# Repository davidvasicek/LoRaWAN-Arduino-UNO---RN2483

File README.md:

# LoRaWAN-Arduino-UNO---RN2483

### Cíl projektu

Tento projekt byl vytvořen za účelem testování LoRaWAN sítě v oblasti Ostravy, kterou v rámci svých cvičení realizují studenti předmětu Radiokomunikační technika/Rádiové sítě vyučovaného na Katedře telekomunikační techniky, VŠB-TU Ostrava.

V rámci tohoto projektu bylo vytvořeno 8 čidel založených na deskách LoRaWAN Arduino UNO s čipem RN2483 napájených stabilizovaným 3V3 napětím devíti voltové externí baterie a integrovaným MicroUSB konektorem. Každý takovýto modul vysílá prostřednictvím LoRaWAN sítě o frekvenci 868 MHz krátký textový řetězec obsahující svou identifikaci, která je směrována na LoRa Gateway (TTN-GW-VSB) a vizualizována v prostředí The Things Network (TTN). Na základě této komunikace je následně možné určit vysílající výkonovou úrověň daných senzorů a tím vytvořit reálnou mapu pokrytí LoRaWAN sítě dané oblasti.

Pro účely testování bylo zapotřebí obejít Duty Cycle modulu RN2483, který nám omezoval zasílání zpráv v kratších intervalech. Každý takovýto modul RN2483 obsahuje vnitřní čítač zabraňující porušení vysílajících oprávnění přesahující 1% vysílající hodiny. Proto byl modul opakovaně resetován, čímž byl vymazán i jeho vnitřní čítač a tím jsme umožnili testování v kratších časových intervalech.

### Specifikace

LoRaWAN Arduino UNO je malý modulek, na jehož horní straně je transceiver RN2483 firmy Microchip, který je zkomunikovaný s procesorem ATmega328p ležícím na spodní straně desky. V procesoru je bootloader Arduino UNO (možno adaptovat na NANO). Modul je přímo přizpůsoben pro komunikaci v sítích LoRaWAN (více info na things.cz nebo na stránkách Českých Radiokomunikací a.s.). K dispozici jsou tato rozhraní: [1]
-	6 digitálních vstupů/výstupů
-	1 digitální vstup s přerušením pro low power režim
-	1 analogový vstup/výstup
-	vstup pro UART/USB převodník
-	anténní konektor SMA samice (na přání možno osadit U.FL IPX konektorem pro vyvedení antény pigtailem)

**Napájení:**
-	flash mód 5V
-	provozní mód 3,3V (bateriové napájení v rozmezí 2,4V až 4,1V)

**Naměřená spotřeba:**
-	power down mód cca 20uA
-	normální režim cca 25mA
-	vysílací špička cca 120mA

### Tutoriál

Výsledkem tohoto tutoriálu je čidlo založené na desce LoRaWAN Arduino UNO s vysílacím modulem RN2483 umožňující zasílaní krátkých zpráv prostřednictvím bezdrátové technologie LoRa. Tyto zprávy mohou obsahovat například informace o okolních teplotách získávány z externího teplotního senzoru, které je možné k desce LoRaWAN Arduino UNO připojit, nebo informace z mnoha jiných senzorů kompatibilních s touto deskou.

Kompletní tutoriál naleznete ve formátu .pdf [zde](https://github.com/davidvasicek/LoRaWAN-Arduino-UNO---RN2483/blob/master/LoRaWAN-Arduino-UNO---RN2483_tutorial.pdf)
                                                                                        
### Obsah adresáře

- **LoRa_RN5.brd** - DPS LoRaWAN Arduino UNO (Eagle)
- **LoRa_RN5.sch** - schéma LoRaWAN Arduino UNO (Eagle)
- **RN2483-Arduino-Library-master.zip** - knihovna pro RN2483 dostupná [zde](https://github.com/jpmeijers/RN2483-Arduino-Library)
- **LoRaWAN-Arduino-UNO---RN2483_code.ino** - kód pro Arduino IDE
- **LoRaWAN-Arduino-UNO---RN2483_tutorial.pdf** - tutoriál
- **LoRaDHT22** - ukázkový kód pro připojení teplotního čidla DHT22 k LoRaWAN Arduino UNO
- **IMG_LoRaWAN-Arduino-UNO.jpg** - foto vytvořených čidel
- **IMG_LoRaWAN-Arduino-UNO_1.jpg** - foto vytvořených čidel

### Užitečné odkazy

- Specifikace LoRaWAN Arduino UNO - RN2483 - e-shop [zde](https://www.arduinotech.cz/produkt/lorawan-arduino-uno/)
- Specifikace RN2483 [zde](http://ww1.microchip.com/downloads/en/DeviceDoc/50002346C.pdf)
- Popis technologie LoRa [zde](http://www.raycom.cz/data/article/filemanager/LoRa.pdf)
- Článek LPWAN - LoRaWAN, Sigfox - vítejte v IoT! [zde](https://www.arduinotech.cz/inpage/lpwan-lorawan-sigfox-vitejte-v-iot/)
- Článek LoRaWAN Arduino UNO s transceiverem RHF76 [zde](https://www.arduinotech.cz/inpage/lorawan-arduino-uno-s-transceiverem-rhf76/)

### Zdroje

- [1] [https://www.arduinotech.cz/produkt/lorawan-arduino-uno/](https://www.arduinotech.cz/produkt/lorawan-arduino-uno/)

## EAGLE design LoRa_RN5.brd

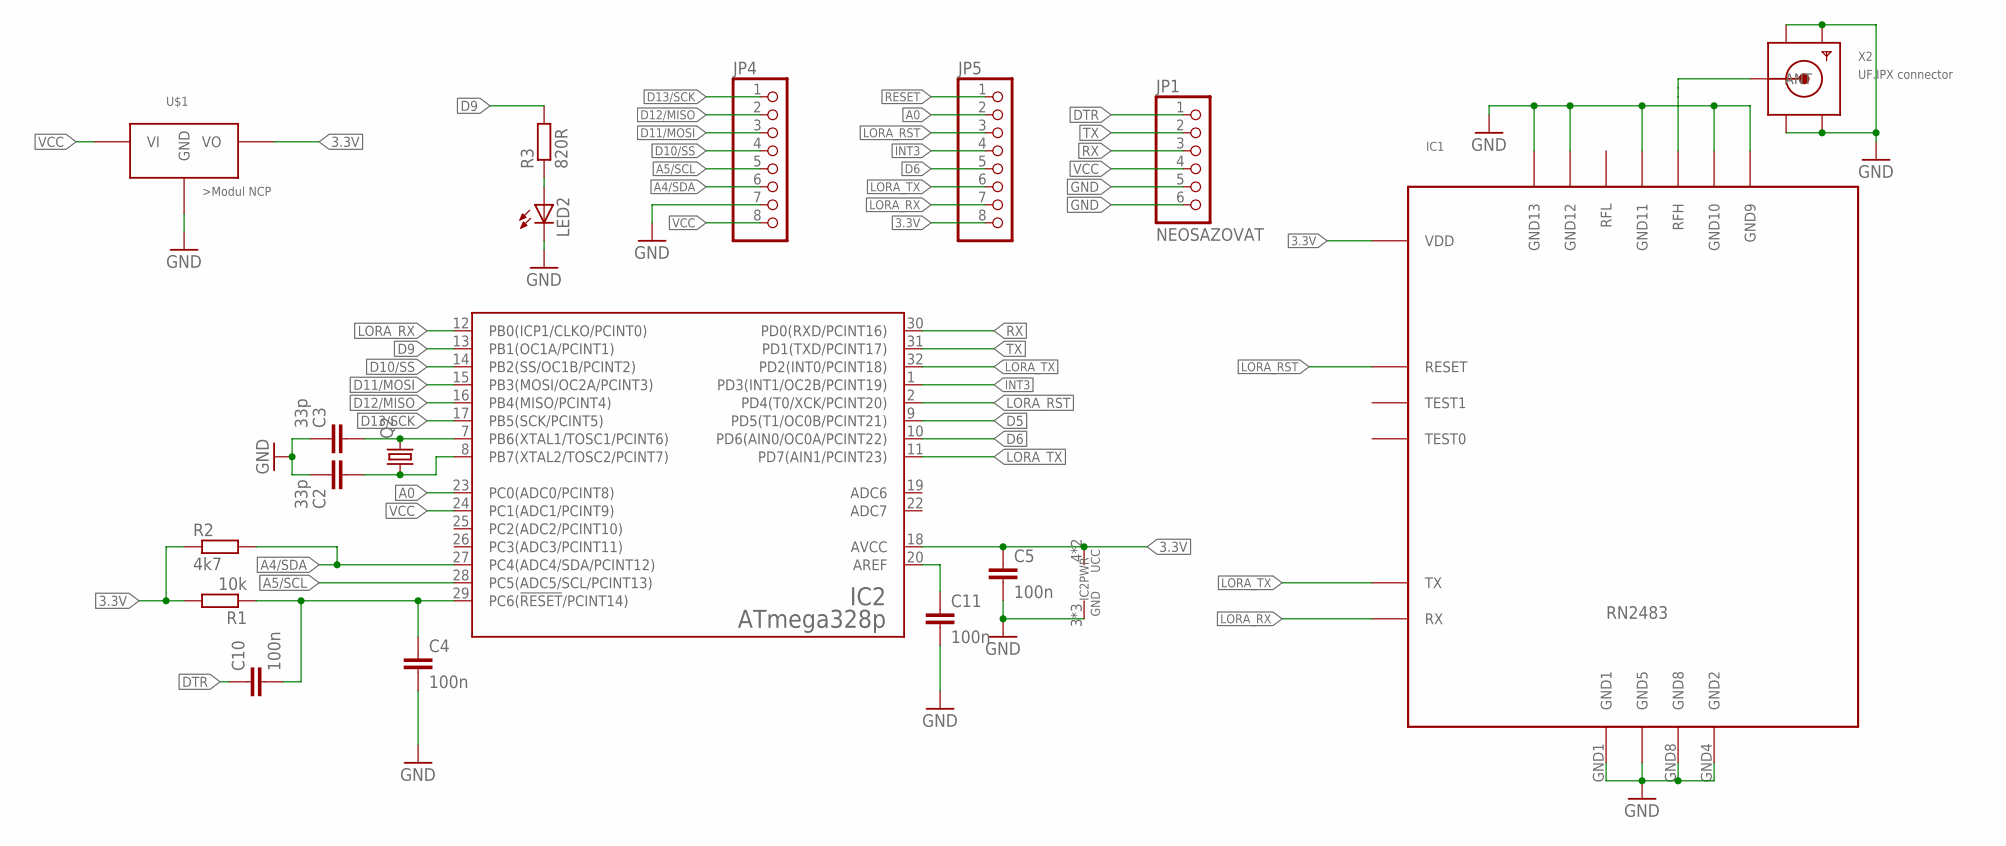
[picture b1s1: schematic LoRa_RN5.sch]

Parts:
C2, C3: 33p; C0805
C4, C5, C10, C11: 100n; C0805
IC1: RN2483_MIN; RN2483_2
IC2: ATmega328p; TQFP32-08
JP1: NEOSAZOVAT; 1X06
JP4, JP5: PINHD-1X8; 1X08
LED2: LEDCHIPLED_1206; CHIPLED_1206
Q2: CRYSTALCTS406; CTS406
R1: 10k; R0805
R2: 4k7; R0805
R3: 820R; R0805
U$1: NEOSAZOVAT; MOD_NCP1402
X2: UF.IPX connector; SMA_EDGELAUNCH_UFL

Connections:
3.3V: C5.1, IC1.VDD, IC2.4 (UCC), IC2.6 (UCC), IC2.18 (AVCC), JP5.8, R1.2, R2.1, U$1.VO
A0: IC2.23 (PC0(ADC0/PCINT8)), JP5.2
A4/SDA: IC2.27 (PC4(ADC4/SDA/PCINT12)), JP4.6, R2.2
A5/SCL: IC2.28 (PC5(ADC5/SCL/PCINT13)), JP4.5
D5: IC2.9 (PD5(T1/OC0B/PCINT21))
D6: IC2.10 (PD6(AIN0/OC0A/PCINT22)), JP5.5
D9: IC2.13 (PB1(OC1A/PCINT1)), R3.2
D10/SS: IC2.14 (PB2(SS/OC1B/PCINT2)), JP4.4
D11/MOSI: IC2.15 (PB3(MOSI/OC2A/PCINT3)), JP4.3
D12/MISO: IC2.16 (PB4(MISO/PCINT4)), JP4.2
D13/SCK: IC2.17 (PB5(SCK/PCINT5)), JP4.1
DTR: C10.1, JP1.1
GND: C2.1, C3.1, C4.2, C5.2, C11.2, IC1.GND1, IC1.GND4 (GND2), IC1.GND5, IC1.GND8, IC1.GND9, IC1.GND10, IC1.GND11, IC1.GND12, IC1.GND13, IC2.3 (GND), IC2.5 (GND), IC2.21 (GND), JP1.5, JP1.6, JP4.7, LED2.C, U$1.GND, X2.GND@1 (GND1), X2.GND@2 (GND2), X2.GND@3 (GND3), X2.GND@4 (GND4)
INT3: IC2.1 (PD3(INT1/OC2B/PCINT19)), JP5.4
LORA_RST: IC1.RESET, IC2.2 (PD4(T0/XCK/PCINT20)), JP5.3
LORA_RX: IC1.RX, IC2.12 (PB0(ICP1/CLKO/PCINT0)), JP5.7
LORA_TX: IC1.TX, IC2.11 (PD7(AIN1/PCINT23)), IC2.32 (PD2(INT0/PCINT18)), JP5.6
unnamed: IC1.RFH, X2.P (ANT)
unnamed: C2.2, IC2.8 (PB7(XTAL2/TOSC2/PCINT7)), Q2.1
unnamed: C3.2, IC2.7 (PB6(XTAL1/TOSC1/PCINT6)), Q2.3 (2)
unnamed: LED2.A, R3.1
unnamed: C11.1, IC2.20 (AREF)
RESET: C4.1, C10.2, IC2.29 (PC6(!RESET!/PCINT14)), JP5.1, R1.1
RX: IC2.30 (PD0(RXD/PCINT16)), JP1.3
TX: IC2.31 (PD1(TXD/PCINT17)), JP1.2
VCC: IC2.24 (PC1(ADC1/PCINT9)), JP1.4, JP4.8, U$1.VI

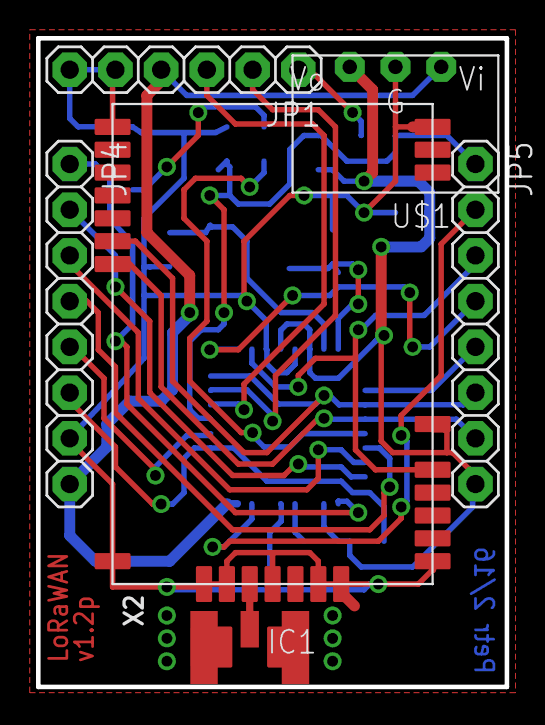
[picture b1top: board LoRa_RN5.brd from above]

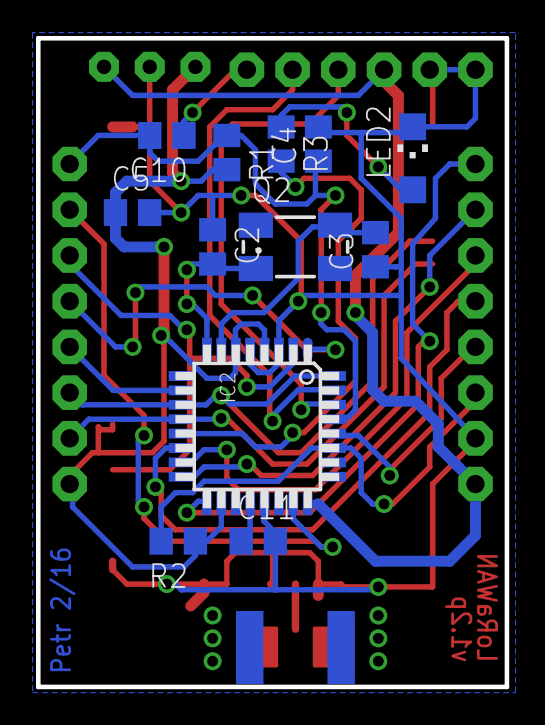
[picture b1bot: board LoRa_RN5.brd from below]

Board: 2 copper layers, 26.0 x 36.0 mm, 18 parts (12 on the bottom side), 25 nets.
